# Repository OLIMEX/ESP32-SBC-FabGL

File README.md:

# ESP32-SBC-FabGL
ESP32-WROVER board working with FabGL library

Software used our fork of FabGL: https://github.com/OLIMEX/FabGL

Product page: https://www.olimex.com/Products/Retro-Computers/ESP32-SBC-FabGL/open-source-hardware

## License
* Hardware is released under CERN OHL v1.2 license
* Software is released under GPL3 License
* Documentation is released under CC BY-SA 3.0

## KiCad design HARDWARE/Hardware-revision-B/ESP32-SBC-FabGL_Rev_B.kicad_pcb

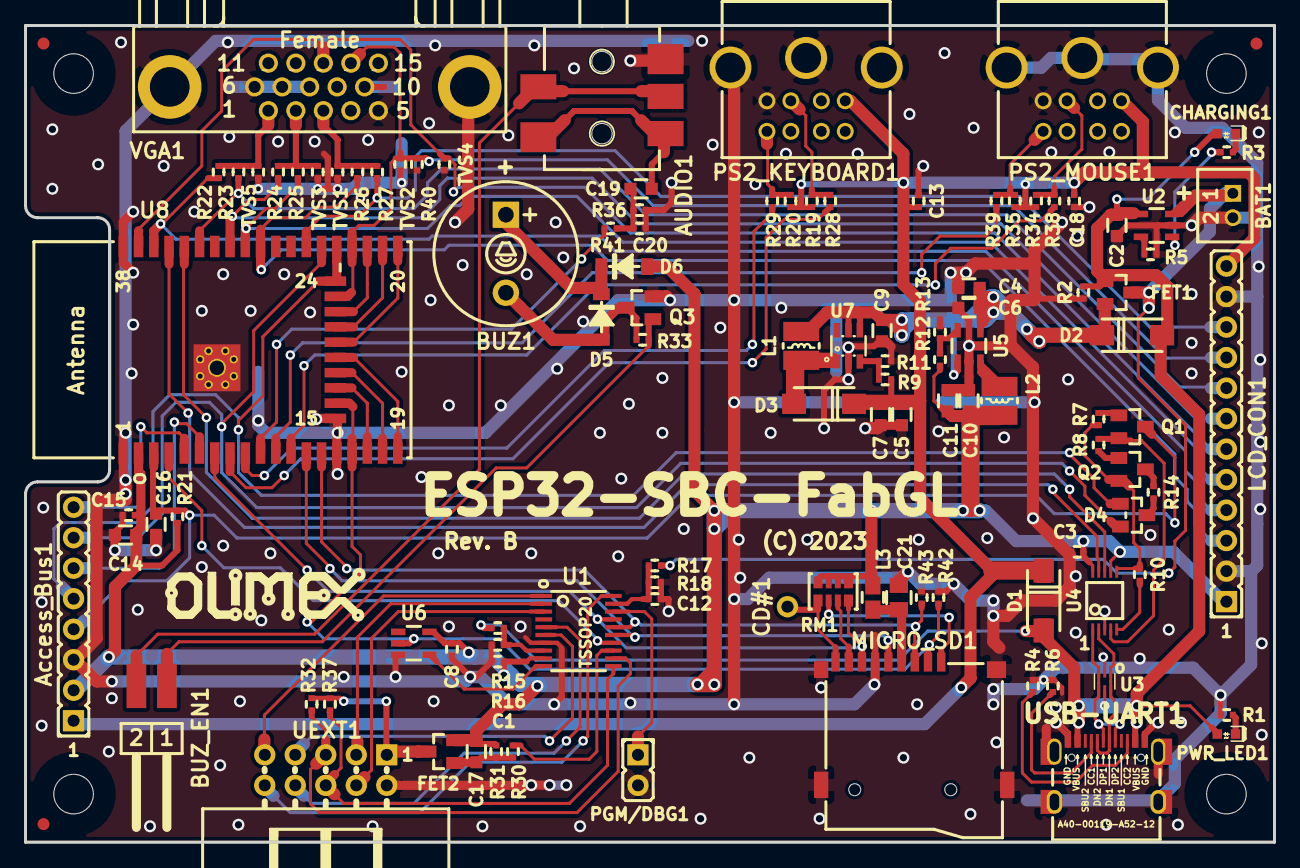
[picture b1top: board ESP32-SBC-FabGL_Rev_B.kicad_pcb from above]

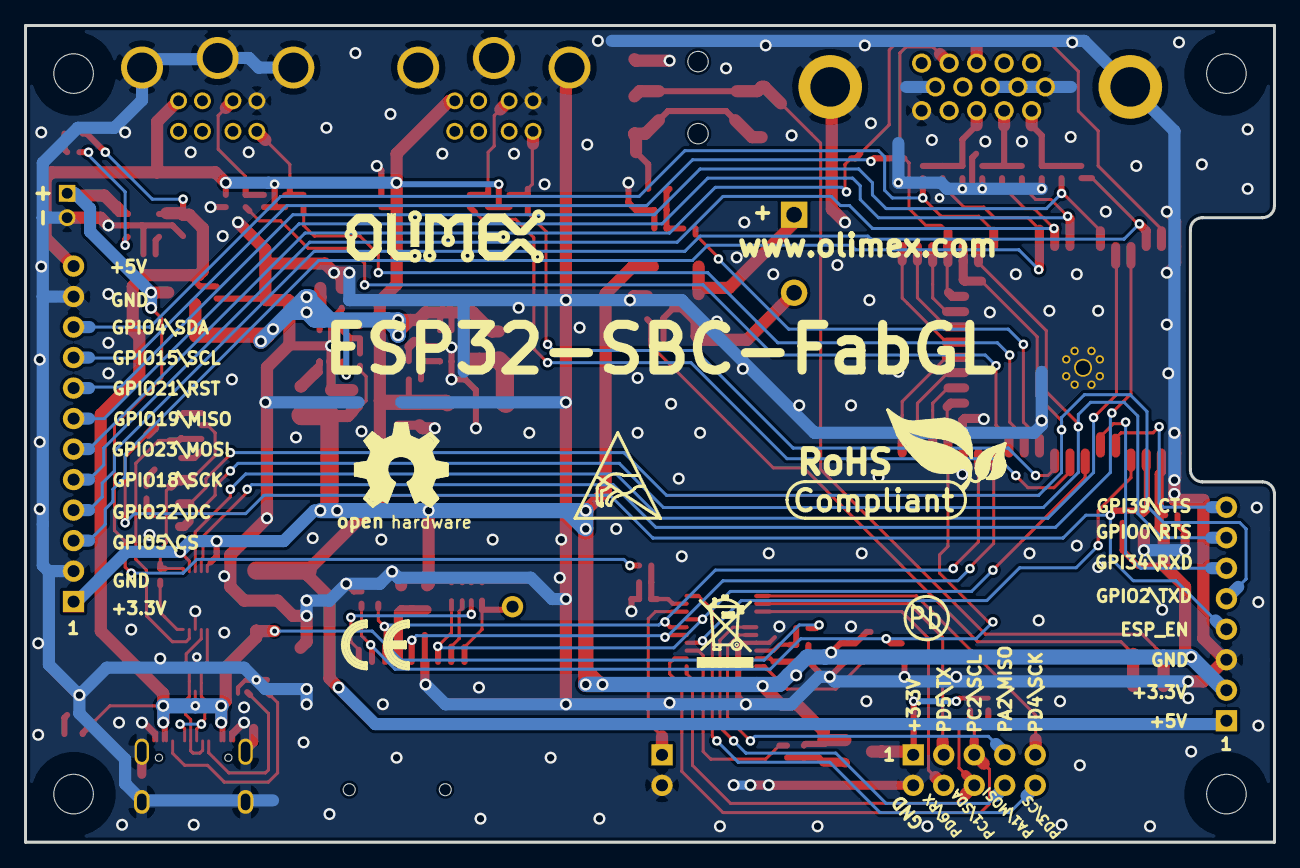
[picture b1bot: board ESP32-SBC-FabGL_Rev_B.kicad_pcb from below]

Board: 2 copper layers, 104.0 x 68.0 mm, 123 parts (7 on the bottom side), 82 nets.

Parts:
AUDIO1: PJ-3.5-365-5P; SCJ325P00XG0B02G
Access_Bus1: HN1x8
BAT1: DW02S; LIPO_BAT_VERTICAL_DW02S
BUZ1: BUZZER_PB1221P(1.1-1.7V_2kHz_12MM); PB1221P_1-Plus_2-Minus
BUZ_EN1: H-WX-1x2-LF+MJ6; HN1x2(SMD)_H-WX-1x2-LF
C1, C3, C8, C12, C13, C15, C18, C20: 100nF/10V/10%/X7R/C0402; C_0402_5MIL_DWS
C2, C6, C7, C9, C10, C14, C17, C19: 22uF/6.3V/20%/X5R/C0603; C_0603_5MIL_DWS
C4, C5, C11: NA(22uF/6.3V/20%/X5R/C0603); C_0603_5MIL_DWS
C16: 1uF/10V/20%/X5R/C0603; C_0603_5MIL_DWS
C21: 47uF/6.3V/20%/X5R/C0805; C_0805_5MIL_DWS
CD#1: TESTPAD; TEST_PAD_40x70_Round
CHARGING1: LED/YELLOW/0603; LED_0603_KA
D1: NA(1N5822/SS34/SMA); SMA-KA
D2, D3: 1N5822/SS34/SMA; SMA-KA
D4: BAT54C(SOT23-3); SOT23-3
D5, D6: 1N4148W/SOD123; SOD-123_1C-2A_KA
FET1, FET2: WPM2015-3/TR; SOT23
FID1, FID2, FID3: Fiducial; Fiducial1x3
L1, L2: 2.2uH/NRS3015T2R2MNGH; CD32
L3: FB0805/600R/2A; L_0805_5MIL_DWS
LCD_CON1: HN1x12
Logo_OLIMEX_TB-Bottom: Logo_OLIMEX_TB
Logo_OLIMEX_TB-Top: Logo_OLIMEX_TB
MH1, MH2, MH3, MH4: Mounting_Hole_NPTH; Mounting_Hole_Drill-3.3mm_Clerance-7mm
MICRO_SD1: TFC-WPAPR-08-LF; TFC-WPAPR-08
PGM/DBG1: NA(HN1x2); HN1x2
PS2_KEYBOARD1, PS2_MOUSE1: MDR6_MINI-DIN; PS2_MDR6_MINI-DIN
PWR_LED1: LED/RED/0603; LED_0603_KA
Q1, Q2, Q3: BC817-40(SOT23); SOT23
R1, R3, R30, R32, R33, R37: 2.2k/R0402; R_0402_5MIL_DWS
R2, R5, R19, R20, R21, R34, R35, R43: 10k/R0402; R_0402_5MIL_DWS
R4, R6: 5.1k/1%/R0402; R_0402_5MIL_DWS
R7, R8: 1k/R0402; R_0402_5MIL_DWS
R9: 8.25k/1%/R0402; R_0402_5MIL_DWS
R10: 4.7k/R0402; R_0402_5MIL_DWS
R11: 1.1k/1%/R0402; R_0402_5MIL_DWS
R12, R15, R31: 220k/R0402; R_0402_5MIL_DWS
R13: 49.9k/1%/R0402; R_0402_5MIL_DWS
R14, R36: 150R/R0402; R_0402_5MIL_DWS
R16, R17, R42: 470k/R0402; R_0402_5MIL_DWS
R18: 150k/R0402; R_0402_5MIL_DWS
R22, R24, R26: 430R/1%/R0402; R_0402_5MIL_DWS
R23, R25, R27: 866R/1%/R0402; R_0402_5MIL_DWS
R28, R29, R38, R39: 120R/R0402; R_0402_5MIL_DWS
R40: NA/R0402; R_0402_5MIL_DWS
R41: 270R/R0402; R_0402_5MIL_DWS
RM1: RA1206_(4x0603)_4B8_10k; RA1206_(4X0603)_4B8_xx
Sign_Antistatic: Sign_Antistatic
Sign_CE: CE_Sign
Sign_OSHW_8x8: Sign_OSHW_8x8
Sign_PB-Free: Sign_PB-Free
Sign_RecycleBin: Sign_RecycleBin; Sign_RecycleBin_1
Sign_RoHS: Sign_RoHS; Sign_RoHS_1
TVS1, TVS2, TVS3, TVS4, TVS5: NA(GG0402052R542P); D_0402_5MIL_DWS
U1: CH32V003F4P6(TSSOP20); TSSOP20_Pitch-0.65mm_6.6x4.5x1.2mm
U2: BL4054B-42TPRN(SOT23-5); SOT-23-5
U3: NA(USBLC6-2P6); SOT-666
U4: CH340X(MSOP-10); MSOP-10_Pitch-0.5mm_3.00x3.00x1.00mm
U5: SY8089AAAC(SOT23-5); SOT-23-5
U6: SN74LVC1G04DBVR(SOT23-5); SOT-23-5
U7: MT3608(SOT23-6); SOT23-6
U8: ESP32-WROVER-E; ESP32-WROVER(WROOM)-UNIVERSAL_MODULE
UEXT1: B-R-10-LF(BH10R); BH10R
USB-UART1: USB-C-16P-F(A40-00119-A52-12); USB2.0_TYPE-C(A40-00119-A52-12)_Paste
VGA1: HDR15-3.08-14.5T/VGA15/14.5mm; VGA15-F(HDR15-3.08-14.5T)

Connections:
+3.3V: Access_Bus1.2, C1.2, C3.1, C8.1, C10.1, C11.1, C14.1, C15.2, C17.1, D6.2, FET2.2, L2.2, L3.1, LCD_CON1.1, R12.2, R21.1, R31.1, RM1.1.1, RM1.2.1, RM1.3.1, RM1.4.1, U1.9, U4.7, U4.10, U6.5, U8.2
+5V: Access_Bus1.1, C5.1, C7.1, C13.1, C18.1, D1.1, D3.1, LCD_CON1.12, PS2_KEYBOARD1.4, PS2_MOUSE1.4, R9.1, R19.1, R20.1, R34.1, R35.1
+5V_USB: C2.1, CHARGING1.2, D1.2, D2.2, FET1.1, PWR_LED1.2, R2.1, R15.1, U2.4, U3.5, USB-UART1.A4, USB-UART1.A9, USB-UART1.B4, USB-UART1.B9
/BUZZER: AUDIO1.4, AUDIO1.5, BUZ_EN1.2
/CC1: R6.2, USB-UART1.A5
/CC2: R4.2, USB-UART1.B5
/DTR#: Q2.2, R7.1, R10.2, U4.6
/D_Com: Q2.3, R14.2
/ESP_EN: Access_Bus1.4, C16.1, Q1.3, R21.2, U8.3
/GPI34\U1RXD: Access_Bus1.6, U8.6
/GPI35\HSPI_MISO: MICRO_SD1.7, RM1.1.2, U1.17, U8.7
/GPI36\IO_EXP_IRQ: U1.14, U8.4
/GPI39\U1CTS: Access_Bus1.8, U8.5
/GPIO0\U1RTS: Access_Bus1.7, D4.2, U8.25
/GPIO1\U0TXD: U4.9, U8.35
/GPIO2\U1TXD: Access_Bus1.5, D4.1, U8.24
/GPIO3\U0RXD: U4.8, U8.34
/GPIO4\Blue_0\I2C_SDA: LCD_CON1.10, R27.2, U8.26
/GPIO5\Blue_1\VSPI_CS: LCD_CON1.3, R26.2, U8.29
/GPIO12\HSPI_MOSI: MICRO_SD1.3, R43.2, U1.16, U8.14
/GPIO13\HSPI_CS: MICRO_SD1.2, R42.2, U6.2, U8.16
/GPIO14\HSPI_CLK: MICRO_SD1.5, U1.15, U8.13
/GPIO15\VSync\I2C_SCL: LCD_CON1.9, R40.1, TVS2.2, U8.23, VGA1.14
/GPIO18\Green_0\VSPI_SCK: LCD_CON1.5, R25.2, U8.30
/GPIO19\Green_1\VSPI_MISO: LCD_CON1.7, R24.2, U8.31
/GPIO21\Red_0\LCD_RST: LCD_CON1.8, R23.2, U8.33
/GPIO22\Red_1\LCD_DC: LCD_CON1.4, R22.2, U8.36
/GPIO23\HSync\VSPI_MOSI: LCD_CON1.6, TVS4.2, U8.37, VGA1.13
/GPIO25\AUDIO: R41.2, U8.10
/GPIO26\MOUSE_CLK: R39.2, U8.11
/GPIO27\MOUSE_DAT: R38.2, U8.12
/GPIO32\KBD_DAT: R28.2, U8.8
/GPIO33\KBD_CLK: R29.2, U8.9
/PA1\SoftSPI_MOSI: U1.5, UEXT1.8
/PA2\SoftSPI_MISO: U1.6, UEXT1.7
/PC1\SDA: R37.2, U1.11, UEXT1.6
/PC2\SCL: R32.2, U1.12, UEXT1.5
/PC3\UEXT_PWR_EN#: R30.2, U1.13
/PD0\PWR_SENS: R15.2, R16.1, U1.8
/PD1\SWIO: PGM/DBG1.1, U1.18
/PD2\BAT_SENS: C12.2, R17.2, R18.1, U1.19
/PD3\SoftSPI_CS#: U1.20, UEXT1.10
/PD4\SoftSPI_SCK: U1.1, UEXT1.9
/PD5\UTX: U1.2, UEXT1.3
/PD6\URX: U1.3, UEXT1.4
/RTS#: Q1.2, R8.1, U4.4
/USB_D+: U3.3, U3.4, U4.1, USB-UART1.A6, USB-UART1.B6
/USB_D-: U3.1, U3.6, U4.2, USB-UART1.A7, USB-UART1.B7
GND: AUDIO1.2, Access_Bus1.3, BAT1.2, C1.1, C2.2, C3.2, C4.2, C5.2, C6.2, C7.2, C8.2, C9.2, C10.2, C11.2, C12.1, C13.2, C14.2, C15.1, C16.2, C18.2, C20.2, C21.2, LCD_CON1.2, LCD_CON1.11, MICRO_SD1.6, MICRO_SD1.10, MICRO_SD1.11, MICRO_SD1.12, MICRO_SD1.13, PGM/DBG1.2, PS2_KEYBOARD1.3, PS2_KEYBOARD1.9, PS2_MOUSE1.3, PS2_MOUSE1.9, Q3.2, R1.2, R2.2, R4.1, R5.2, R6.1, R11.2, R13.2, R16.2, R18.2, R36.2, R40.2, R42.1, R43.1, TVS1.1, TVS2.1, TVS3.1, TVS4.1, TVS5.1, U1.7, U2.2, U3.2, U4.3, U5.2, U6.3, U7.2, U8.1, U8.15, U8.38, U8.39, UEXT1.2, USB-UART1.0, USB-UART1.A1, USB-UART1.A12, USB-UART1.B1, USB-UART1.B12, VGA1.5, VGA1.6, VGA1.7, VGA1.8, VGA1.10, VGA1.16, VGA1.17
unnamed: AUDIO1.1, AUDIO1.3, C19.2
unnamed: BUZ1.1, D5.1, D6.1
unnamed: BUZ1.2, D5.2, Q3.3, R33.2
unnamed: BUZ_EN1.1, Q3.1, R33.1
unnamed: C4.1, C6.1, C9.1, D2.1, FET1.2, L1.2, U5.1, U5.4, U7.4, U7.5
unnamed: C17.2, FET2.1, R30.1, R31.2
unnamed: C19.1, C20.1, R36.1, R41.1
unnamed: C21.1, L3.2, MICRO_SD1.4
unnamed: CD#1.1, MICRO_SD1.9, RM1.4.2
unnamed: CHARGING1.1, R3.1
unnamed: D3.2, L1.1, U7.1
unnamed: D4.3, R14.1
unnamed: FET2.3, R32.1, R37.1, UEXT1.1
unnamed: L2.1, U5.3
unnamed: MICRO_SD1.1, RM1.3.2
unnamed: MICRO_SD1.8, RM1.2.2
unnamed: PS2_KEYBOARD1.1, R19.2, R28.1
unnamed: PS2_KEYBOARD1.5, R20.2, R29.1
unnamed: PS2_MOUSE1.1, R34.2, R38.1
unnamed: PS2_MOUSE1.5, R35.2, R39.1
unnamed: PWR_LED1.1, R1.1
unnamed: Q1.1, R7.2
unnamed: Q2.1, R8.2
unnamed: R3.2, U2.1
unnamed: R5.1, U2.5
unnamed: R10.1, U4.5
unnamed: R9.2, R11.1, U7.3
unnamed: R12.1, R13.1, U5.5
unnamed: R22.1, R23.1, TVS5.2, VGA1.1
unnamed: R24.1, R25.1, TVS3.2, VGA1.2
unnamed: R26.1, R27.1, TVS1.2, VGA1.3
unnamed: U1.10, U6.4
VBAT: BAT1.1, FET1.3, R17.1, U2.3

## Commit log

2023-07-03 CH32V003 Firmware
2023-07-03 CH32V003 and WiiNunchuk drivers
2023-07-03 README
2023-07-04 Update
    Schematic and design
2023-07-04 Update
    Links
2023-07-31 CH32V003 expander improvements
2023-07-31 Prebuilt files
    Added prebuilt binary, hex and elf file for the existing versions of the firmware (0.9 and 1.0)
2023-07-31 Added CH32V0003 programming stuff
2023-08-01 Typo
2023-08-01 CH32V003 Turbo Pascal GPIO example
2023-08-02 add Nunchuck pascal code
2023-12-06 adding stl files and 3mf project for 3d printable case
2024-04-25 Update
    Added manual and next revision changes

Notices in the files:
HARDWARE/Hardware-revision-B/ESP32-SBC-FabGL_Rev_B.kicad_pcb:
(C) 2023
